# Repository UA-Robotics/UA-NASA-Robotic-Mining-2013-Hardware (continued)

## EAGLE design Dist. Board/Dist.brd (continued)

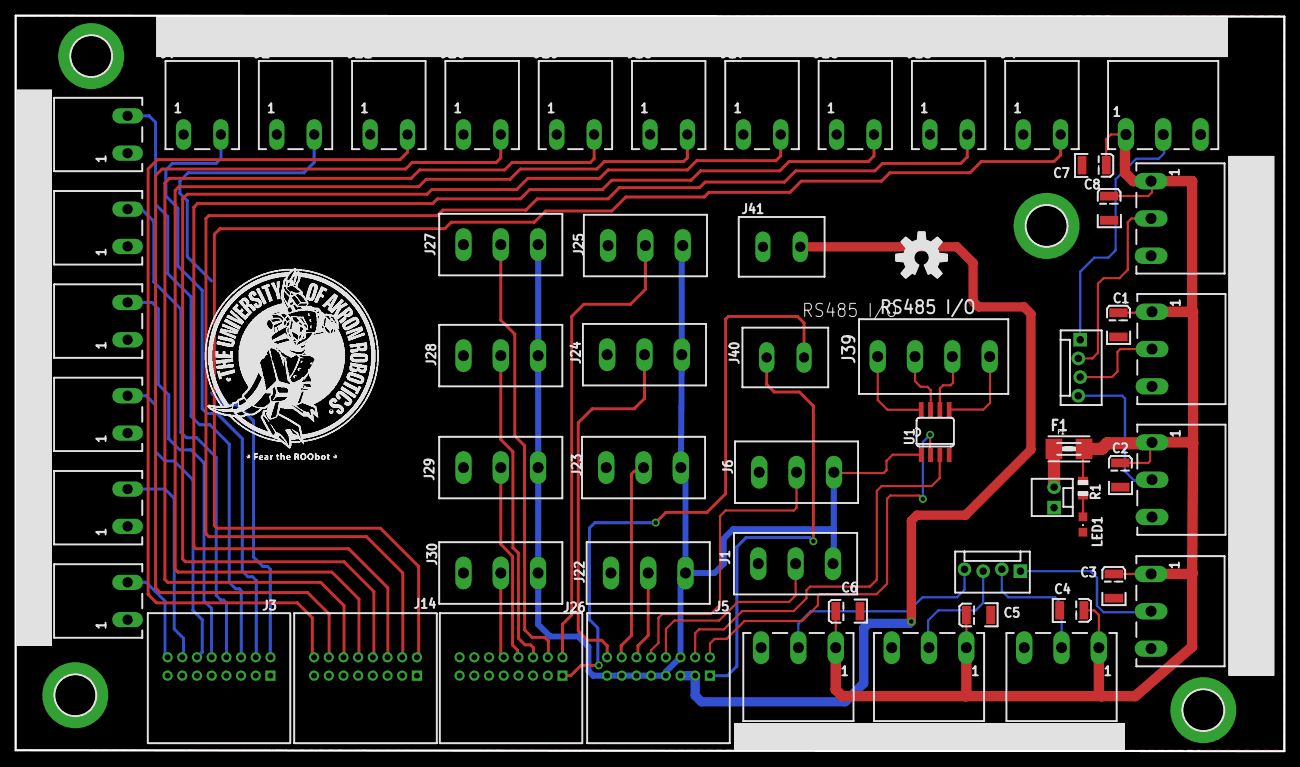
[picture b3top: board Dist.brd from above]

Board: 2 copper layers, 172.7 x 100.1 mm, 62 parts (0 on the bottom side), 47 nets.

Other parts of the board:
U$2: ROOBOT1

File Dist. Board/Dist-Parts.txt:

Partlist

Exported from Dist.sch at 1/16/2013 11:27:02 PM

EAGLE Version 6.2.0 Copyright (c) 1988-2012 CadSoft

Assembly variant: 

Part     Value              Device             Package        Library  Sheet

C1                          CAP_POL3528        EIA3528        SparkFun 1
C2                          CAP_POL3528        EIA3528        SparkFun 1
C3                          CAP_POL3528        EIA3528        SparkFun 1
C4                          CAP_POL3528        EIA3528        SparkFun 1
C5                          CAP_POL3528        EIA3528        SparkFun 1
C6                          CAP_POL3528        EIA3528        SparkFun 1
C7                          CAP_POL3528        EIA3528        SparkFun 1
C8                          CAP_POL3528        EIA3528        SparkFun 1
F1                          PTCFUSE-1812       1812           adafruit 1
H1       MOUNT-PAD-ROUND5.5 MOUNT-PAD-ROUND5.5 5,5-PAD        holes    1
H2       MOUNT-PAD-ROUND5.5 MOUNT-PAD-ROUND5.5 5,5-PAD        holes    1
H3       MOUNT-PAD-ROUND5.5 MOUNT-PAD-ROUND5.5 5,5-PAD        holes    1
H4       MOUNT-PAD-ROUND5.5 MOUNT-PAD-ROUND5.5 5,5-PAD        holes    1
J1       EUROMAG-3UP        EUROMAG-3UP        M3-UP          NASA_LIB 1
J2       EUROMAG-290DEG     EUROMAG-290DEG     M2             NASA_LIB 1
J3       0559591630         0559591630         0559591630     NASA_LIB 1
J4       EUROMAG-290DEG     EUROMAG-290DEG     M2             NASA_LIB 1
J5       0559591630         0559591630         0559591630     NASA_LIB 1
J6       EUROMAG-3UP        EUROMAG-3UP        M3-UP          NASA_LIB 1
J7       EUROMAG-290DEG     EUROMAG-290DEG     M2             NASA_LIB 1
J8       EUROMAG-290DEG     EUROMAG-290DEG     M2             NASA_LIB 1
J9       EUROMAG-290DEG     EUROMAG-290DEG     M2             NASA_LIB 1
J10      EUROMAG-290DEG     EUROMAG-290DEG     M2             NASA_LIB 1
J11      EUROMAG-290DEG     EUROMAG-290DEG     M2             NASA_LIB 1
J12      EUROMAG-290DEG     EUROMAG-290DEG     M2             NASA_LIB 1
J13      EUROMAG-290DEG     EUROMAG-290DEG     M2             NASA_LIB 1
J14      0559591630         0559591630         0559591630     NASA_LIB 1
J15      EUROMAG-290DEG     EUROMAG-290DEG     M2             NASA_LIB 1
J16      EUROMAG-290DEG     EUROMAG-290DEG     M2             NASA_LIB 1
J17      EUROMAG-290DEG     EUROMAG-290DEG     M2             NASA_LIB 1
J18      EUROMAG-290DEG     EUROMAG-290DEG     M2             NASA_LIB 1
J19      EUROMAG-290DEG     EUROMAG-290DEG     M2             NASA_LIB 1
J20      EUROMAG-290DEG     EUROMAG-290DEG     M2             NASA_LIB 1
J21      EUROMAG-290DEG     EUROMAG-290DEG     M2             NASA_LIB 1
J22      EUROMAG-3UP        EUROMAG-3UP        M3-UP          NASA_LIB 1
J23      EUROMAG-3UP        EUROMAG-3UP        M3-UP          NASA_LIB 1
J24      EUROMAG-3UP        EUROMAG-3UP        M3-UP          NASA_LIB 1
J25      EUROMAG-3UP        EUROMAG-3UP        M3-UP          NASA_LIB 1
J26      0559591630         0559591630         0559591630     NASA_LIB 1
J27      EUROMAG-3UP        EUROMAG-3UP        M3-UP          NASA_LIB 1
J28      EUROMAG-3UP        EUROMAG-3UP        M3-UP          NASA_LIB 1
J29      EUROMAG-3UP        EUROMAG-3UP        M3-UP          NASA_LIB 1
J30      EUROMAG-3UP        EUROMAG-3UP        M3-UP          NASA_LIB 1
J31      EUROMAG-390DEG     EUROMAG-390DEG     M3             NASA_LIB 1
J32      EUROMAG-390DEG     EUROMAG-390DEG     M3             NASA_LIB 1
J33      EUROMAG-390DEG     EUROMAG-390DEG     M3             NASA_LIB 1
J34      EUROMAG-390DEG     EUROMAG-390DEG     M3             NASA_LIB 1
J35      EUROMAG-390DEG     EUROMAG-390DEG     M3             NASA_LIB 1
J36      EUROMAG-390DEG     EUROMAG-390DEG     M3             NASA_LIB 1
J37      EUROMAG-390DEG     EUROMAG-390DEG     M3             NASA_LIB 1
J38      EUROMAG-390DEG     EUROMAG-390DEG     M3             NASA_LIB 1
JP1                         M02POLAR_LOCK      MOLEX-1X2_LOCK SparkFun 1
JP2                         M04POLAR_LOCK      MOLEX-1X4_LOCK SparkFun 1
JP3                         M04POLAR_LOCK      MOLEX-1X4_LOCK SparkFun 1
LED1                        LEDCHIPLED_0805    CHIPLED_0805   adafruit 1
R1                          R-US_R0805         R0805          adafruit 1

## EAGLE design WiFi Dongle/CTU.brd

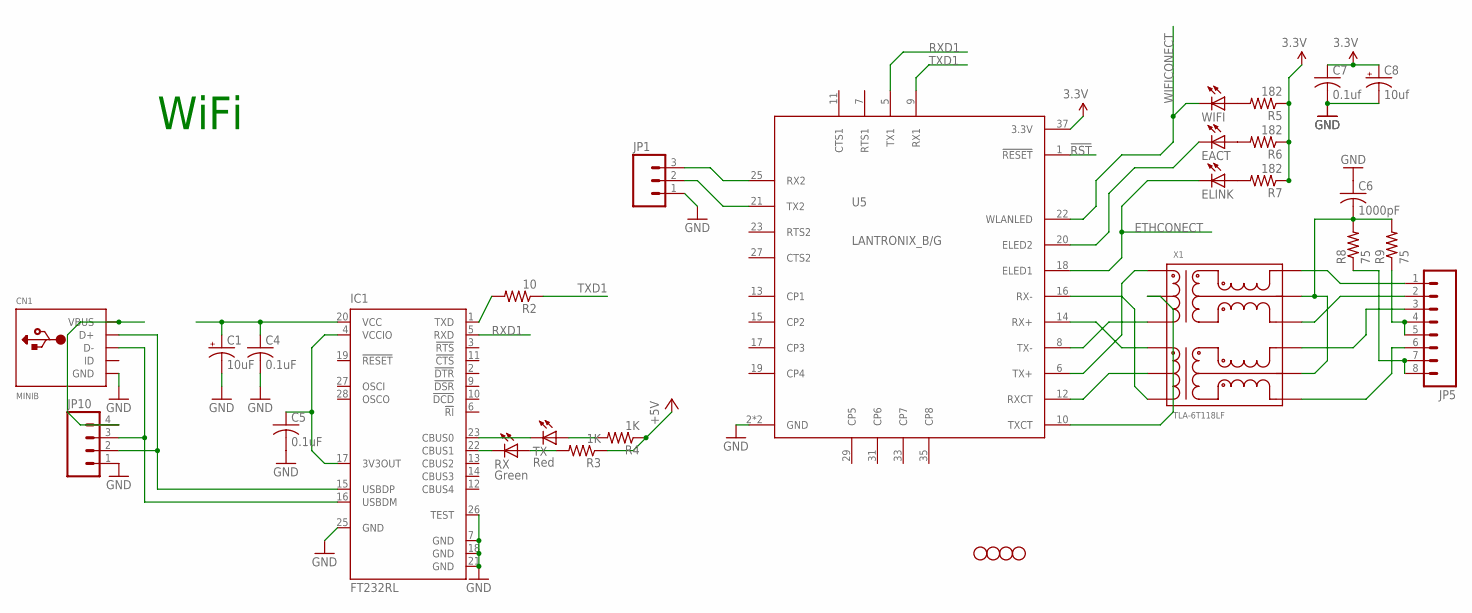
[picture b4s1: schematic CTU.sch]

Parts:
C1: 10uF; EIA3528-KIT
C4, C5: 0.1uF; C0805K
C6: 1000pF; C1812
C7: 0.1uf; C0805K
C8: 10uf; EIA3528
CN1: MINIB; USB-MINIB
EACT: LEDCHIP-LED0805; CHIP-LED0805
ELINK: LEDCHIP-LED0805; CHIP-LED0805
IC1: FT232RL; SSOP28
JP1: M03POLAR; MOLEX-1X3
JP2, JP3, JP4, JP6: STAND-OFF
JP5: M08LOCK_LONGPADS; 1X08_LOCK_LONGPADS
JP10: M04POLAR; MOLEX-1X4
R2: 10; R0805
R3, R4: 1K; R0805
R5, R6, R7: 182; R0805
R8, R9: 75; R0805
RX: Green; CHIP-LED0805
TX: Red; CHIP-LED0805
U5: LANTRONIX_B/G; LANA/BTH
WIFI: LEDCHIP-LED0805; CHIP-LED0805
X1: TLA-6T118LF; SO-16MOD

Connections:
3.3V: C7.1, C8.A (+), R5.1, R6.1, R7.1, U5.37 (3.3V)
!RST: U5.1 (!RESET)
+5V: R3.1, R4.1
ETHCONECT: ELINK.C, U5.18 (ELED1)
GND: C1.C (-), C4.2, C5.2, C6.1, C7.2, C8.C (-), CN1.GND, IC1.7 (GND), IC1.18 (GND), IC1.21 (GND), IC1.25 (GND), IC1.26 (TEST), JP1.1, JP10.1, U5.2 (GND), U5.39 (GND)
unnamed: JP1.2, U5.21 (TX2)
unnamed: JP1.3, U5.25 (RX2)
unnamed: C1.A (+), C4.1, IC1.20 (VCC)
unnamed: CN1.D+, IC1.15 (USBDP), JP10.2
unnamed: CN1.D-, IC1.16 (USBDM), JP10.3
unnamed: IC1.23 (CBUS0), TX.C
unnamed: IC1.22 (CBUS1), RX.C
unnamed: R3.2, RX.A
unnamed: R4.2, TX.A
unnamed: IC1.1 (TXD), R2.2
unnamed: C5.1, IC1.4 (VCCIO), IC1.17 (3V3OUT)
unnamed: U5.8 (TX-), X1.3
unnamed: U5.6 (TX+), X1.1
unnamed: U5.14 (RX+), X1.6
unnamed: U5.16 (RX-), X1.8
unnamed: U5.12 (RXCT), X1.7
unnamed: U5.10 (TXCT), X1.2
unnamed: JP5.4, JP5.5, R9.1
unnamed: JP5.7, JP5.8, R8.1
unnamed: JP5.6, X1.9
unnamed: JP5.3, X1.11
unnamed: JP5.2, X1.14
unnamed: JP5.1, X1.16
unnamed: C6.2, R8.2, R9.2, X1.10, X1.15
unnamed: ELINK.A, R7.2
unnamed: EACT.A, R6.2
unnamed: R5.2, WIFI.A
unnamed: EACT.C, U5.20 (ELED2)
RXD1: IC1.5 (RXD), U5.5 (TX1)
TXD1: R2.1, U5.9 (RX1)
VBUS: CN1.VBUS, JP10.4
WIFICONECT: U5.22 (WLANLED), WIFI.C

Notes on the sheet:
WiFi

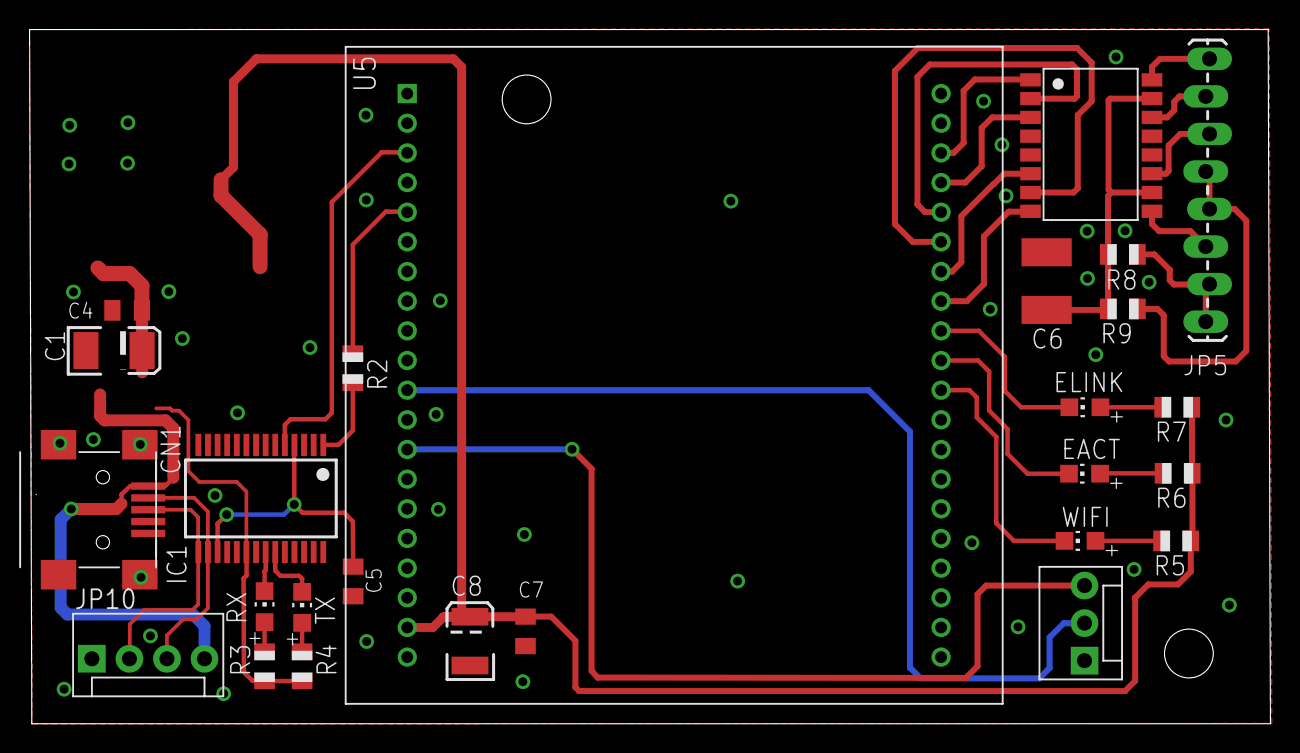
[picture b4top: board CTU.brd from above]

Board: 2 copper layers, 84.0 x 47.0 mm, 30 parts (0 on the bottom side), 36 nets.

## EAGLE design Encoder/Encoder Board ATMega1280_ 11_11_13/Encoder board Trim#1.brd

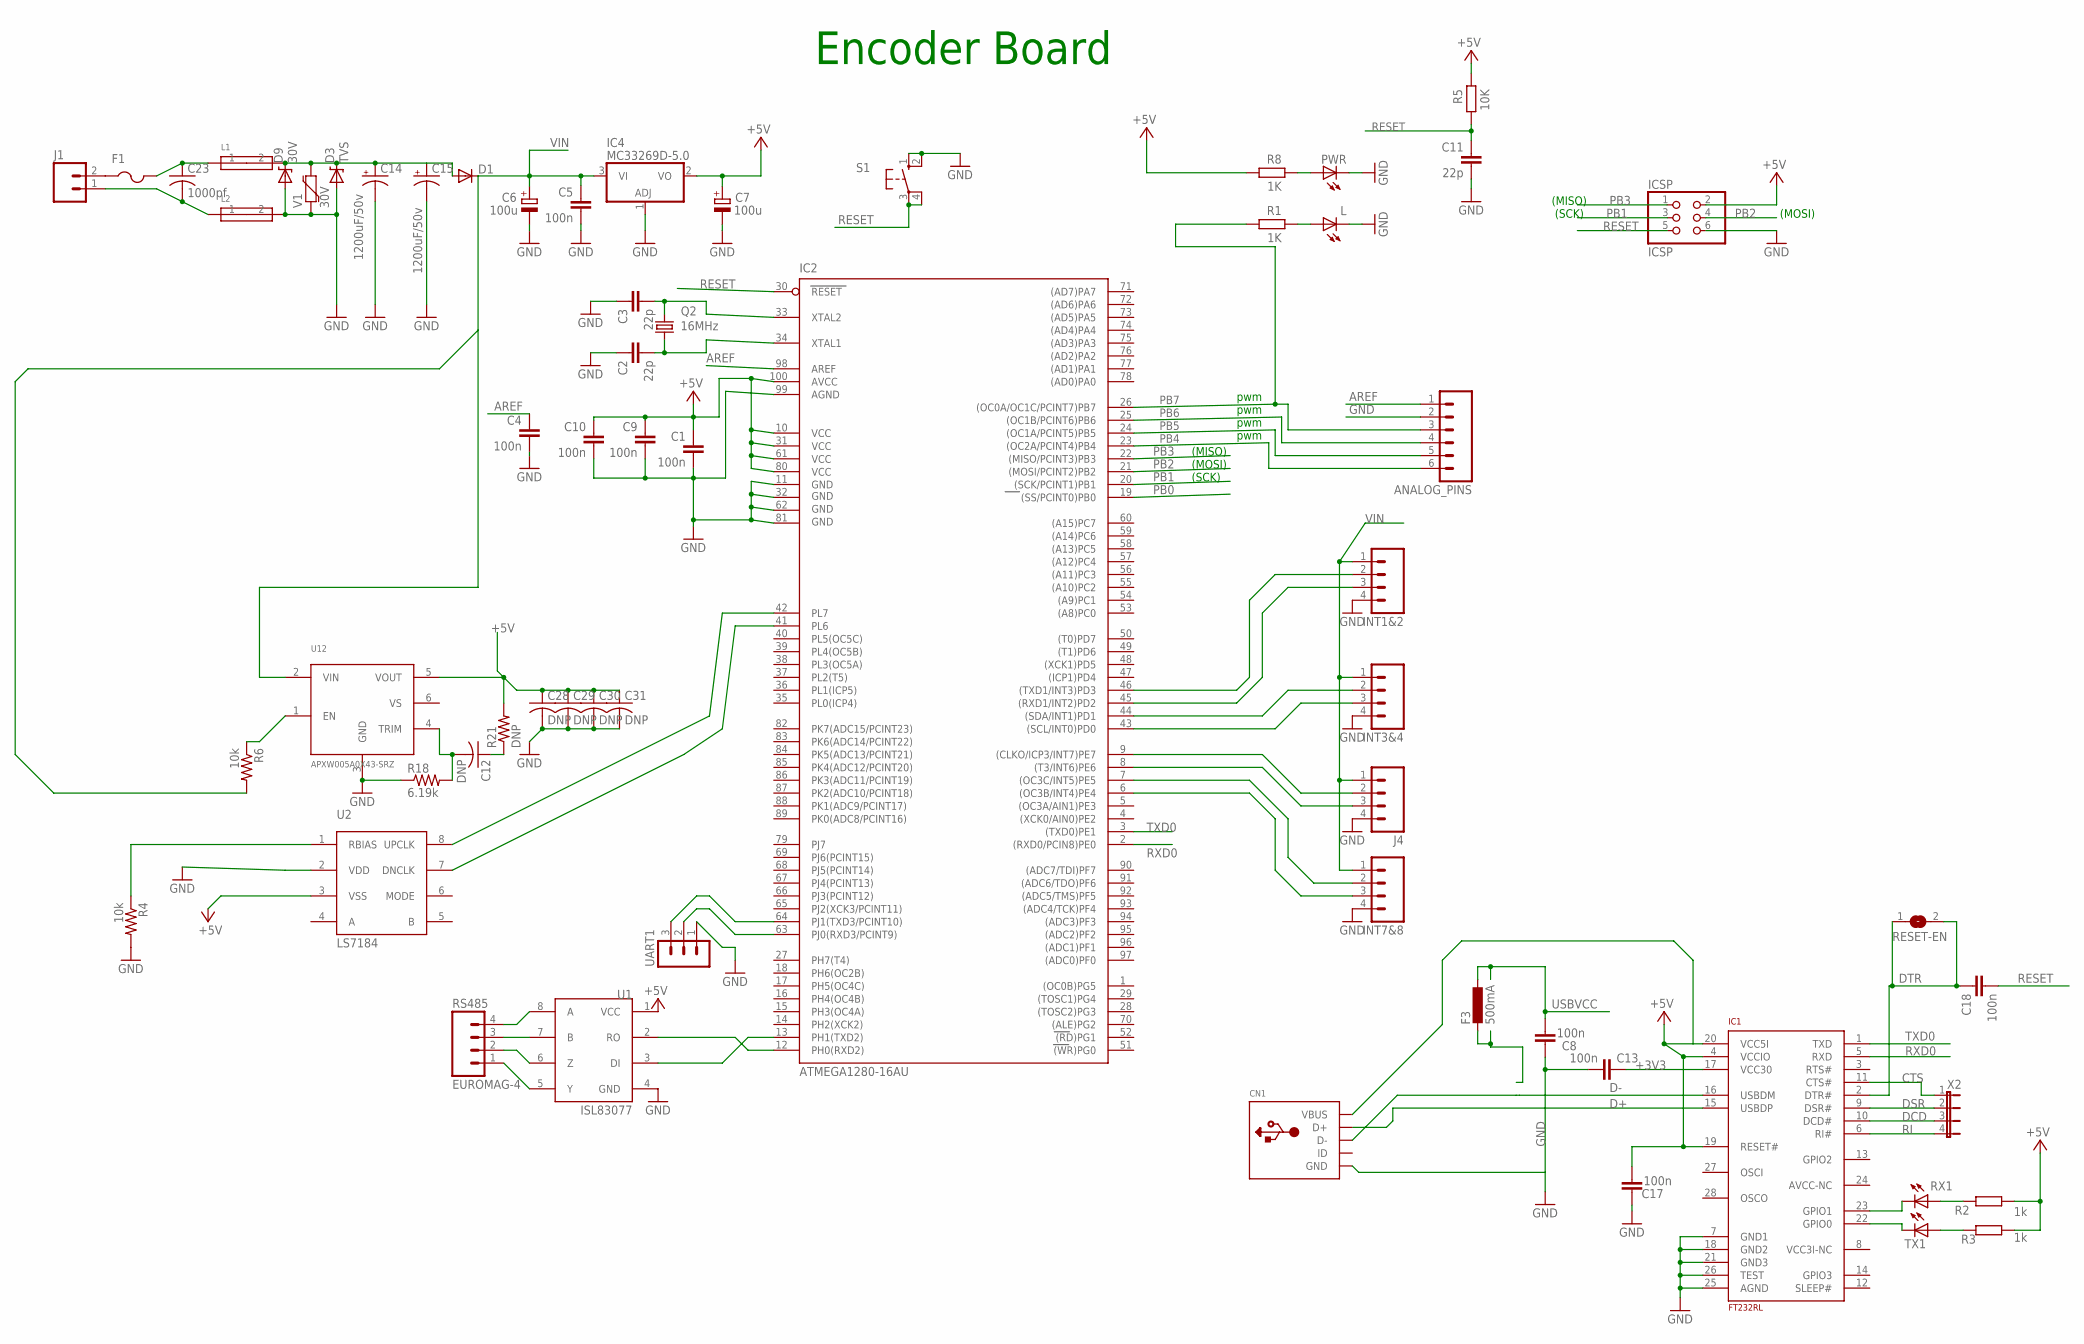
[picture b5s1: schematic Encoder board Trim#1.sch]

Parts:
ANALOG_PINS: M06; 06P
C1, C4, C5, C8, C9, C10, C13, C17, C18: 100n; C0805RND
C2, C3, C11: 22p; C0805RND
C6, C7: 100u; SMC_D
C12, C28, C29, C30, C31: DNP; C0805
C14, C15: 1200uF/50v; CAN_18MM
C23: 1000pf; C1825
CN1: USBMINIB; USB-MINIB
D1: DIODE-SMB; SMB
D3: TVS; DO-214AC
D9: 30V; SMB-DIODE
F1: PTCFUSE-1206; R1206
F3: 500mA; L1812
IC1: FT232RL; SSOP28
IC2: ATMEGA1280-16AU; TQFP100
IC4: MC33269D-5.0; DPACK
ICSP: ICSP; 2X03
INT1&2: M4
INT3&4, INT7&8: M4-90
J1: EUROMAG-290DEG; M2
J4: M4
L: LED0805ROUND; 0805RND
L1, L2: FERITEBEAD; 0603
PWR: LED0805ROUND; 0805RND
Q2: 16MHz; HC49/S
R1, R8: 1K; R0805RND
R2, R3: 1k; R0805RND
R4, R6: 10k; R0805
R5: 10K; R0805RND
R18: 6.19k; R0805
R21: DNP; R0805
RESET-EN: SJ
RS485: EUROMAG-4; M4
RX1: LED0805ROUND; 0805RND
S1: 10-XX; B3F-10XX
TX1: LED0805ROUND; 0805RND
U1: ISL83077; SO08
U2: LS7184; SO08
U12: APXW005A0X43-SRZ
UART1: MA03-1
V1: 30V; 0603-RES
X2: JP4E; JP4

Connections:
+3V3: C13.2, IC1.17 (VCC30)
+5V: C1.1, C7.+, C9.1, C10.1, C17.1, C28.1, C29.1, C30.1, C31.1, CN1.VBUS, IC1.4 (VCCIO), IC1.19 (RESET#), IC1.20 (VCC5I), IC2.10 (VCC), IC2.31 (VCC1), IC2.61 (VCC2), IC2.80 (VCC3), IC2.100 (AVCC), IC4.2 (VO), ICSP.2, R2.2, R3.2, R5.2, R8.1, R21.2, U1.1 (VCC), U2.3 (VSS), U12.5 (VOUT)
AREF: ANALOG_PINS.1, C4.1, IC2.98 (AREF)
CTS: IC1.11 (CTS#), X2.1
D+: IC1.15 (USBDP)
D-: CN1.D-, IC1.16 (USBDM)
DCD: IC1.10 (DCD#), X2.3
DSR: IC1.9 (DSR#), X2.2
DTR: C18.1, IC1.2 (DTR#), RESET-EN.1, RESET-EN.2
GND: ANALOG_PINS.2, C1.2, C2.1, C3.1, C4.2, C5.2, C6.-, C7.-, C8.2, C9.2, C10.2, C11.2, C13.1, C14.-, C15.-, C17.2, C28.2, C29.2, C30.2, C31.2, CN1.GND, D3.A, D9.A, IC1.7 (GND1), IC1.18 (GND2), IC1.21 (GND3), IC1.25 (AGND), IC1.26 (TEST), IC2.11 (GND), IC2.32 (GND1), IC2.62 (GND2), IC2.81 (GND3), IC2.99 (AGND), IC4.1 (ADJ), ICSP.6, INT1&2.4, INT3&4.4, INT7&8.4, J4.4, L.P$2 (C), L2.2, PWR.P$2 (C), R4.2, R18.1, S1.1 (S), S1.2 (S1), U1.4 (GND), U2.2 (VDD), U12.3 (GND), UART1.1, V1.1
INT5&6: IC2.8 ((T3/INT6)PE6), J4.3
INT7&8: IC2.6 ((OC3B/INT4)PE4), INT7&8.3
unnamed: IC2.46 ((TXD1/INT3)PD3), INT1&2.2
unnamed: L.P$1 (A), R1.2
unnamed: PWR.P$1 (A), R8.2
unnamed: IC2.45 ((RXD1/INT2)PD2), INT1&2.3
unnamed: IC2.44 ((SDA/INT1)PD1), INT3&4.2
unnamed: C2.2, IC2.34 (XTAL1), Q2.1
unnamed: C3.2, IC2.33 (XTAL2), Q2.2
unnamed: IC2.43 ((SCL/INT0)PD0), INT3&4.3
unnamed: IC2.9 ((CLKO/ICP3/INT7)PE7), J4.2
unnamed: IC2.63 (PJ0(RXD3/PCINT9)), UART1.2
unnamed: R4.1, U2.1 (RBIAS)
unnamed: F1.1, J1.2
unnamed: IC2.7 ((OC3C/INT5)PE5), INT7&8.2
unnamed: IC2.64 (PJ1(TXD3/PCINT10)), UART1.3
unnamed: IC2.42 (PL7), U2.8 (UPCLK)
unnamed: IC1.23 (GPIO1), RX1.P$2 (C)
unnamed: IC2.13 (PH1(TXD2)), U1.3 (DI)
unnamed: IC2.12 (PH0(RXD2)), U1.2 (RO)
unnamed: RS485.4, U1.8 (A)
unnamed: RS485.3, U1.7 (B)
unnamed: IC1.22 (GPIO0), TX1.P$2 (C)
unnamed: RS485.1, U1.5 (Y)
unnamed: R2.1, RX1.P$1 (A)
unnamed: R3.1, TX1.P$1 (A)
unnamed: IC2.41 (PL6), U2.7 (DNCLK)
unnamed: R6.1, U12.1 (EN)
unnamed: C23.2, J1.1, L2.1
unnamed: C14.+, C15.+, D1.A, D3.C, D9.C, L1.2, V1.2
unnamed: C12.2, R18.2, U12.4 (TRIM)
unnamed: C12.1, R21.1
PB0: IC2.19 ((SS/PCINT0)PB0)
PB1: IC2.20 ((SCK/PCINT1)PB1), ICSP.3
PB2: IC2.21 ((MOSI/PCINT2)PB2), ICSP.4
PB3: IC2.22 ((MISO/PCINT3)PB3), ICSP.1
PB4: ANALOG_PINS.6, IC2.23 ((OC2A/PCINT4)PB4)
PB5: ANALOG_PINS.5, IC2.24 ((OC1A/PCINT5)PB5)
PB6: ANALOG_PINS.4, IC2.25 ((OC1B/PCINT6)PB6)
PB7: ANALOG_PINS.3, IC2.26 ((OC0A/OC1C/PCINT7)PB7), R1.1
RESET: C11.1, C18.2, IC2.30 (RESET), ICSP.5, R5.1, S1.3, S1.4 (P1)
RI: IC1.6 (RI#), X2.4
RS485: RS485.2, U1.6 (Z)
RXD0: IC1.5 (RXD), IC2.2 ((RXD0/PCIN8)PE0)
TXD0: IC1.1 (TXD), IC2.3 ((TXD0)PE1)
USBVCC: C8.1, F3.1
VIN: C5.1, C6.+, D1.C, IC4.3 (VI), INT1&2.1, INT3&4.1, INT7&8.1, J4.1, R6.2, U12.2 (VIN)
VOL: C23.1, L1.1

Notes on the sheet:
(SCK)
(MISO)
(MOSI)
pwm
Encoder Board

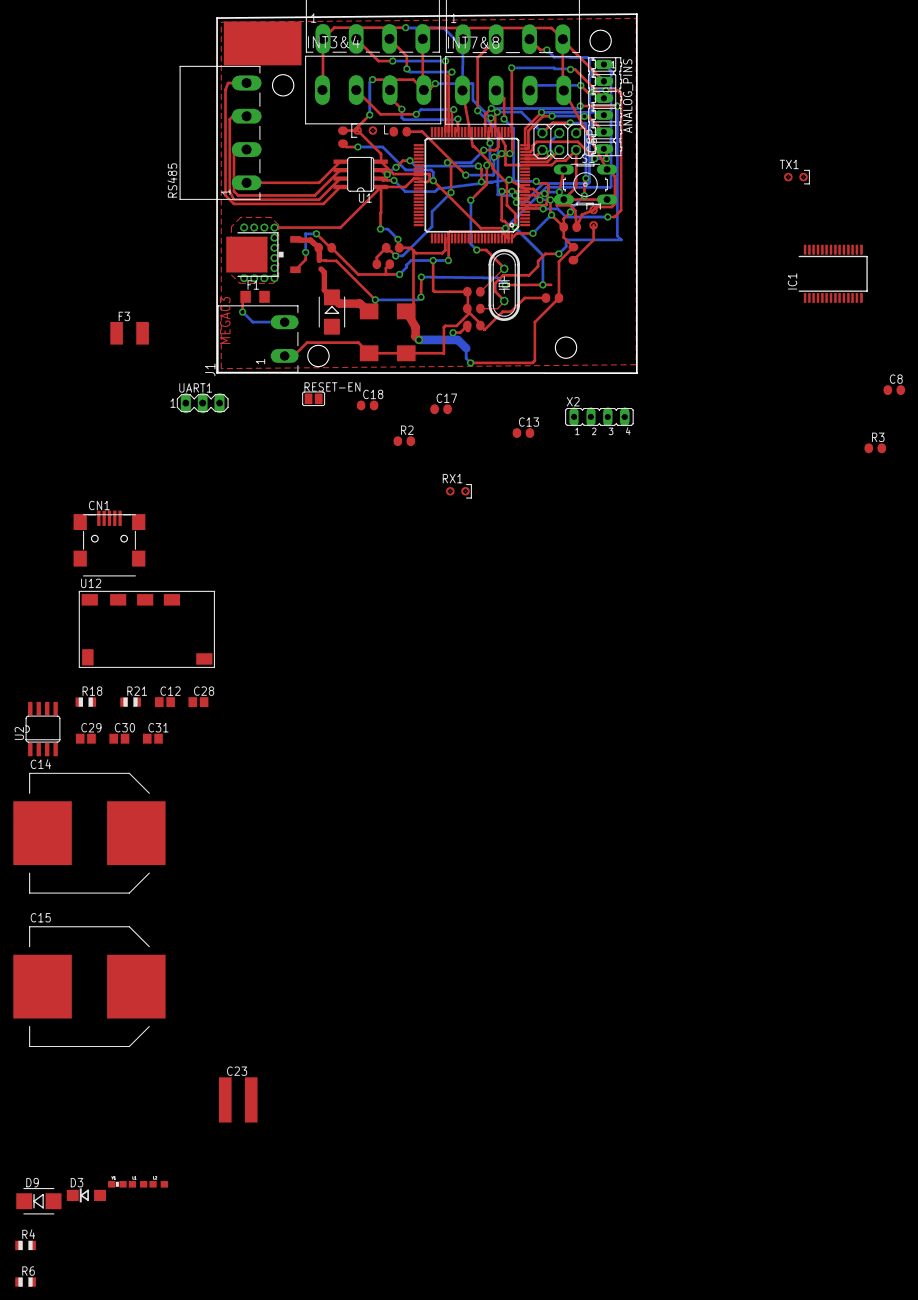
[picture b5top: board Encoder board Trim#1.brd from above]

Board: 2 copper layers, 63.1 x 54.0 mm, 63 parts (0 on the bottom side), 56 nets.

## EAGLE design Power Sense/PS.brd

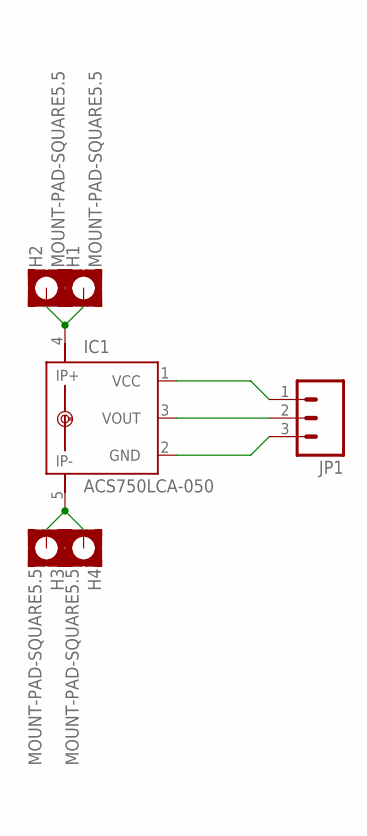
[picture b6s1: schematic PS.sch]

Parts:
H1, H2, H3, H4: MOUNT-PAD-SQUARE5.5; 5,5-PAD-SQUARE
IC1: ACS750LCA-050; ACS75050
JP1: M03POLAR_LOCK; MOLEX-1X3_LOCK

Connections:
unnamed: IC1.1 (VCC), JP1.1
unnamed: IC1.3 (VOUT), JP1.2
unnamed: IC1.2 (GND), JP1.3
unnamed: H3.B5,5, H4.B5,5, IC1.5 (IP-)
unnamed: H1.B5,5, H2.B5,5, IC1.4 (IP+)

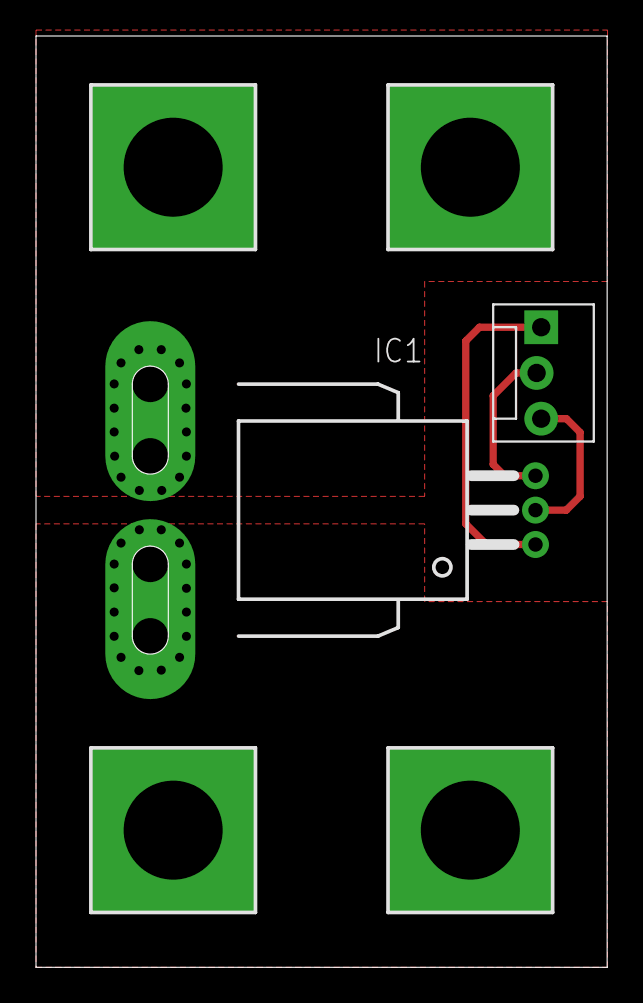
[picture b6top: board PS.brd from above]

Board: 2 copper layers, 31.7 x 51.7 mm, 6 parts (0 on the bottom side), 5 nets.

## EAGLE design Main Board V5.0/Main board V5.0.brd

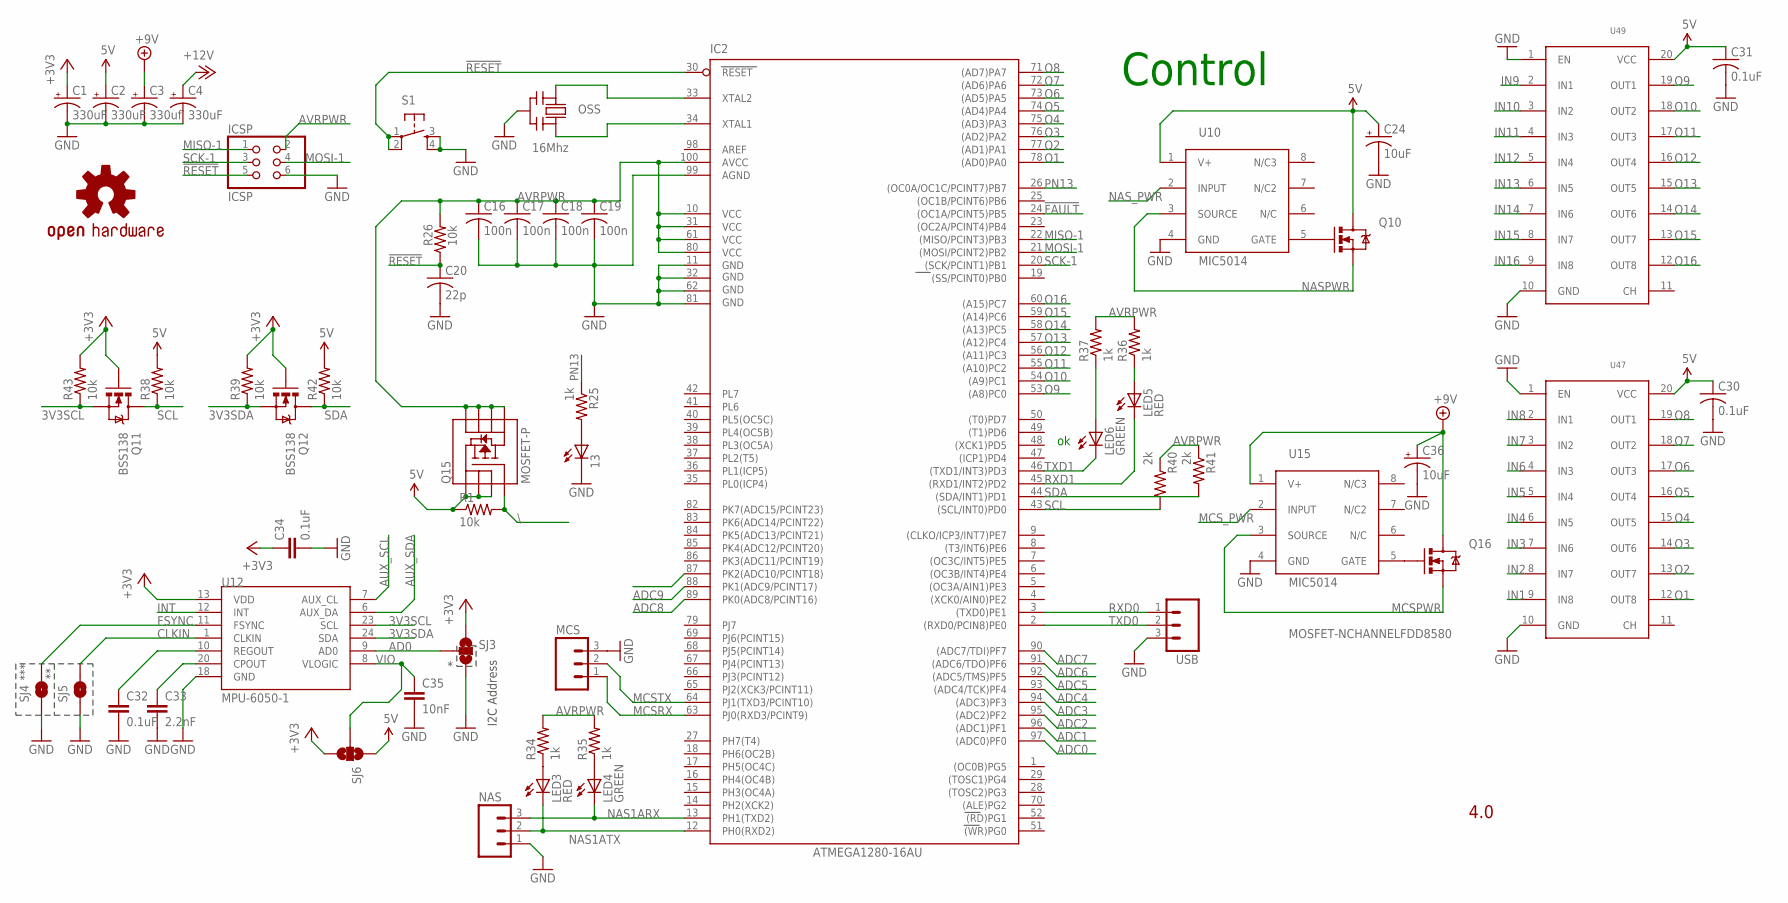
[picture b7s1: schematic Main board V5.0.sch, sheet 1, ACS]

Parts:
13: LEDCHIP-LED0805; CHIP-LED0805
C1, C2, C4: 330uF; 140CLH-0810
C3: 330uf; 140CLH-0810
C16, C17, C18, C19: 100n; C0805
C20: 22p; C0805
C24, C36: 10uF; CT6032
C30, C31: 0.1uF; C0805
C32, C34: 0.1uF; 0805
C33: 2.2nF; 0805
C35: 10nF; 0805
IC2: ATMEGA1280-16AU; TQFP100
ICSP: ICSP; 2X03
LED3, LED5: RED; CHIP-LED0805
LED4, LED6: GREEN; CHIP-LED0805
MCS: M03LOCK; 1X03_LOCK
NAS: M03POLAR; MOLEX-1X3
OSS: 16Mhz; AWCSR
Q10, Q16: MOSFET-NCHANNELFDD8580; DPAK
Q11, Q12: BSS138; SOT23-3
Q15: MOSFET-P; SO08
R1, R26, R38, R39, R42, R43: 10k; R0805
R25, R34, R35, R36, R37: 1k; R0805
R40, R41: 2k; R0805
S1: TAC_SWITCHSMD; TACTILE_SWITCH_SMD
SJ3, SJ6: SOLDERJUMPER_2WAYPASTE2&3; SJ_3_PASTE2&3
SJ4, SJ5: SOLDERJUMPERTRACE; SJ_2S-TRACE
U10, U15: MIC5014; SO08
U12: MPU-6050-1; QFN-24-4MM2
U47, U49: MAX6818; SSOP-20
U$3: OSHW-LOGOL; OSHW-LOGO-L
USB: M03LOCK; 1X03_LOCK

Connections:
3V3SCL: Q11.2 (S), R43.1, U12.23 (SCL)
3V3SDA: Q12.2 (S), R39.1, U12.24 (SDA)
5V: C2.+, C24.+, C30.1, C31.1, Q10.4 (D), Q15.1 (S), Q15.2 (S), Q15.3 (S), R1.1, R38.2, R42.2, SJ6.1, U10.1 (V+), U47.20 (VCC), U49.20 (VCC); also elsewhere on the board
!FAULT: IC2.24 ((OC1A/PCINT5)PB5)
!RESET: C20.1, IC2.30 (RESET), ICSP.5, R26.1, S1.1, S1.2
+3V3: C1.+, C34.1, Q11.1 (G), Q12.1 (G), R39.2, R43.2, SJ3.1, SJ6.3, U12.13 (VDD); also elsewhere on the board
+9V: C3.+, C36.+, Q16.4 (D), U15.1 (V+); also elsewhere on the board
+12V: C4.+; also elsewhere on the board
AD0: SJ3.2, U12.9 (AD0)
ADC0: IC2.97 ((ADC0)PF0); also elsewhere on the board
ADC1: IC2.96 ((ADC1)PF1); also elsewhere on the board
ADC2: IC2.95 ((ADC2)PF2); also elsewhere on the board
ADC3: IC2.94 ((ADC3)PF3); also elsewhere on the board
ADC4: IC2.93 ((ADC4/TCK)PF4); also elsewhere on the board
ADC5: IC2.92 ((ADC5/TMS)PF5); also elsewhere on the board
ADC6: IC2.91 ((ADC6/TDO)PF6); also elsewhere on the board
ADC7: IC2.90 ((ADC7/TDI)PF7); also elsewhere on the board
ADC8: IC2.89 (PK0(ADC8/PCINT16)); also elsewhere on the board
ADC9: IC2.88 (PK1(ADC9/PCINT17)); also elsewhere on the board
AUX_SCL: U12.7 (AUX_CL)
AUX_SDA: U12.6 (AUX_DA)
AVRPWR: C16.1, C17.1, C18.1, C19.1, IC2.10 (VCC), IC2.31 (VCC1), IC2.61 (VCC2), IC2.80 (VCC3), IC2.100 (AVCC), ICSP.2, Q15.5 (D), Q15.6 (D), Q15.7 (D), Q15.8 (D), R26.2, R34.2, R35.2, R36.2, R37.2, R40.1, R41.1
CLKIN: SJ5.2, U12.1 (CLKIN)
FSYNC: SJ4.2, U12.11 (FSYNC)
GND: 13.C, C1.-, C2.-, C3.-, C4.-, C16.2, C17.2, C18.2, C19.2, C20.2, C24.-, C30.2, C31.2, C32.2, C33.2, C34.2, C35.2, C36.-, IC2.11 (GND), IC2.32 (GND1), IC2.62 (GND2), IC2.81 (GND3), IC2.99 (AGND), ICSP.6, MCS.3, NAS.1, OSS.2 (GND), S1.3, S1.4, SJ3.3, SJ4.1, SJ5.1, U10.4 (GND), U12.18 (GND), U15.4 (GND), U47.1 (EN), U47.10 (GND), U49.1 (EN), U49.10 (GND), USB.3; also elsewhere on the board
IN1: U47.9 (IN8); also elsewhere on the board
IN2: U47.8 (IN7); also elsewhere on the board
IN3: U47.7 (IN6); also elsewhere on the board
IN4: U47.6 (IN5); also elsewhere on the board
IN5: U47.5 (IN4); also elsewhere on the board
IN6: U47.4 (IN3); also elsewhere on the board
IN7: U47.3 (IN2); also elsewhere on the board
IN8: U47.2 (IN1); also elsewhere on the board
IN9: U49.2 (IN1); also elsewhere on the board
IN10: U49.3 (IN2); also elsewhere on the board
IN11: U49.4 (IN3); also elsewhere on the board
IN12: U49.5 (IN4); also elsewhere on the board
IN13: U49.6 (IN5); also elsewhere on the board
IN14: U49.7 (IN6); also elsewhere on the board
IN15: U49.8 (IN7); also elsewhere on the board
IN16: U49.9 (IN8); also elsewhere on the board
INT: U12.12 (INT)
MCSPWR: Q16.3 (S), U15.3 (SOURCE); also elsewhere on the board
MCSRX: IC2.63 (PJ0(RXD3/PCINT9)), MCS.1; also elsewhere on the board
MCSTX: IC2.64 (PJ1(TXD3/PCINT10)), MCS.2; also elsewhere on the board
MCS_PWR: U15.2 (INPUT); also elsewhere on the board
MISO-1: IC2.22 ((MISO/PCINT3)PB3), ICSP.1
MOSI-1: IC2.21 ((MOSI/PCINT2)PB2), ICSP.4
unnamed: 13.A, R25.2
unnamed: IC2.34 (XTAL1), OSS.3 (OUT)
unnamed: IC2.33 (XTAL2), OSS.1 (IN)
unnamed: C33.1, U12.20 (CPOUT)
unnamed: C32.1, U12.10 (REGOUT)
unnamed: Q10.1 (G), U10.5 (GATE)
unnamed: LED4.A, R35.1
unnamed: LED3.A, R34.1
unnamed: LED6.A, R37.1
unnamed: LED5.A, R36.1
unnamed: Q16.1 (G), U15.5 (GATE)
NAS1ARX: IC2.13 (PH1(TXD2)), LED4.C, NAS.3; also elsewhere on the board
NAS1ATX: IC2.12 (PH0(RXD2)), LED3.C, NAS.2; also elsewhere on the board
NASPWR: Q10.3 (S), U10.3 (SOURCE); also elsewhere on the board
NAS_PWR: U10.2 (INPUT); also elsewhere on the board
O1: IC2.78 ((AD0)PA0), U47.12 (OUT8)
O2: IC2.77 ((AD1)PA1), U47.13 (OUT7)
O3: IC2.76 ((AD2)PA2), U47.14 (OUT6)
O4: IC2.75 ((AD3)PA3), U47.15 (OUT5)
O5: IC2.74 ((AD4)PA4), U47.16 (OUT4)
O6: IC2.73 ((AD5)PA5), U47.17 (OUT3)
O7: IC2.72 ((AD6)PA6), U47.18 (OUT2)
O8: IC2.71 ((AD7)PA7), U47.19 (OUT1)
O9: IC2.53 ((A8)PC0), U49.19 (OUT1)
O10: IC2.54 ((A9)PC1), U49.18 (OUT2)
O11: IC2.55 ((A10)PC2), U49.17 (OUT3)
O12: IC2.56 ((A11)PC3), U49.16 (OUT4)
O13: IC2.57 ((A12)PC4), U49.15 (OUT5)
O14: IC2.58 ((A13)PC5), U49.14 (OUT6)
O15: IC2.59 ((A14)PC6), U49.13 (OUT7)
O16: IC2.60 ((A15)PC7), U49.12 (OUT8)
PN13: IC2.26 ((OC0A/OC1C/PCINT7)PB7), R25.1; also elsewhere on the board
RXD0: IC2.3 ((TXD0)PE1), USB.1
RXD1: IC2.45 ((RXD1/INT2)PD2), LED5.C; also elsewhere on the board
SCK-1: IC2.20 ((SCK/PCINT1)PB1), ICSP.3
SCL: IC2.43 ((SCL/INT0)PD0), Q11.3 (D), R38.1, R40.2; also elsewhere on the board
SDA: IC2.44 ((SDA/INT1)PD1), Q12.3 (D), R41.2, R42.1; also elsewhere on the board
TXD0: IC2.2 ((RXD0/PCIN8)PE0), USB.2
TXD1: IC2.46 ((TXD1/INT3)PD3), LED6.C; also elsewhere on the board
VIO: C35.1, SJ6.2, U12.8 (VLOGIC)
\: Q15.4 (G), R1.2; also elsewhere on the board

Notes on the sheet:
4.0
Control
I2C Address
***

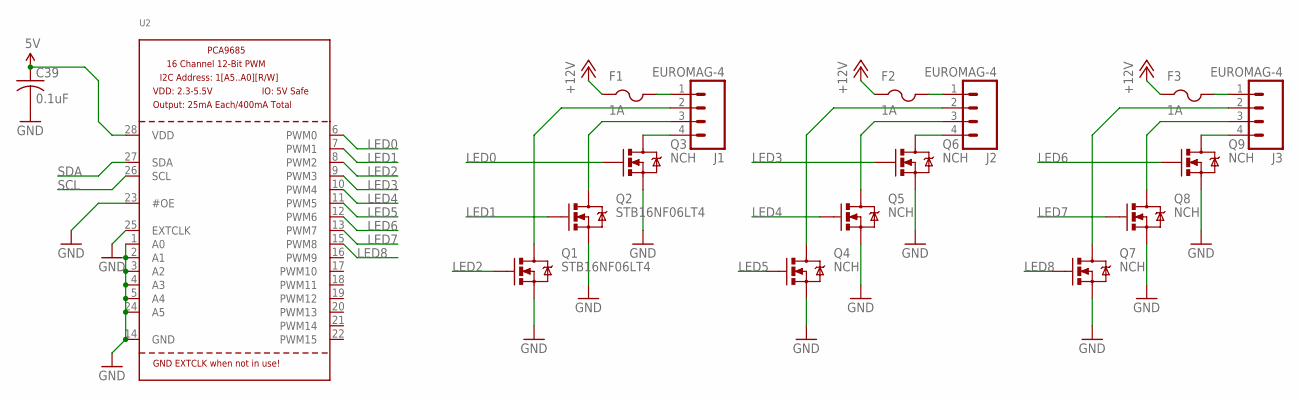
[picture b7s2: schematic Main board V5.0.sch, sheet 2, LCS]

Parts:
C39: 0.1uF; C0603
F1, F2, F3: 1A; 1812
J1, J2, J3: EUROMAG-4; M4
Q1, Q2: STB16NF06LT4; DPAK
Q3, Q4, Q5, Q6, Q7, Q8, Q9: NCH; DPAK
U2: PCA9685; TSSOP28

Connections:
5V: C39.1, U2.28 (VDD); also elsewhere on the board
+12V: F1.1, F2.1, F3.1; also elsewhere on the board
GND: C39.2, Q1.3 (S), Q2.3 (S), Q3.3 (S), Q4.3 (S), Q5.3 (S), Q6.3 (S), Q7.3 (S), Q8.3 (S), Q9.3 (S), U2.1 (A0), U2.2 (A1), U2.3 (A2), U2.4 (A3), U2.5 (A4), U2.14 (GND), U2.23 (#OE), U2.24 (A5), U2.25 (EXTCLK); also elsewhere on the board
LED0: Q3.1 (G), U2.6 (PWM0)
LED1: Q2.1 (G), U2.7 (PWM1)
LED2: Q1.1 (G), U2.8 (PWM2)
LED3: Q6.1 (G), U2.9 (PWM3)
LED4: Q5.1 (G), U2.10 (PWM4)
LED5: Q4.1 (G), U2.11 (PWM5)
LED6: Q9.1 (G), U2.12 (PWM6)
LED7: Q8.1 (G), U2.13 (PWM7)
LED8: Q7.1 (G), U2.15 (PWM8)
unnamed: J1.4, Q3.4 (D)
unnamed: J1.3, Q2.4 (D)
unnamed: J1.2, Q1.4 (D)
unnamed: F1.2, J1.1
unnamed: J2.4, Q6.4 (D)
unnamed: J2.3, Q5.4 (D)
unnamed: J2.2, Q4.4 (D)
unnamed: F2.2, J2.1
unnamed: J3.4, Q9.4 (D)
unnamed: J3.3, Q8.4 (D)
unnamed: J3.2, Q7.4 (D)
unnamed: F3.2, J3.1
SCL: U2.26 (SCL); also elsewhere on the board
SDA: U2.27 (SDA); also elsewhere on the board
